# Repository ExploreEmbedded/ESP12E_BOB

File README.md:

# ESP12E_BOB

The ESP8266 ESP12E Wifi Module is now more user friendly with the Explore ESP8266 Wi-Fi Module. It aptly fits on a breadboard 
with all pins taken out. The module goes into programming mode with a single reset switch. 
<a href = "https://www.exploreembedded.com/product/Explore%20ESP8266%20Wi-Fi%20Module">Click here</a> for more details.

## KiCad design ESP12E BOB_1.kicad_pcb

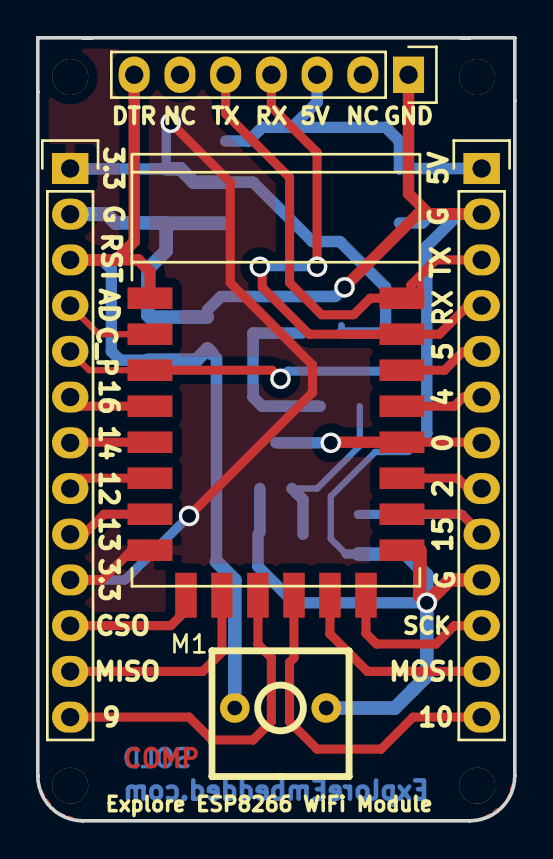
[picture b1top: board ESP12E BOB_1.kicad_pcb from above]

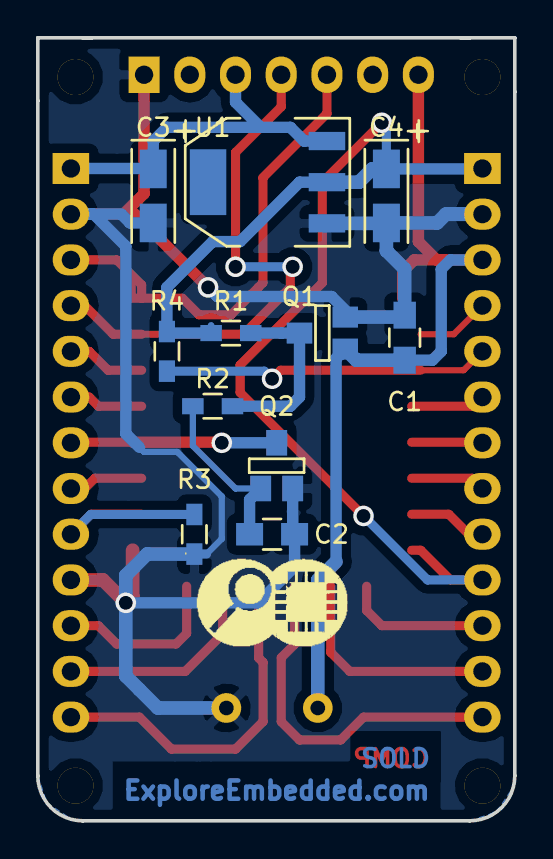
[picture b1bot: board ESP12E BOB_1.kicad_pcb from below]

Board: 2 copper layers, 26.5 x 43.5 mm, 21 parts (12 on the bottom side), 25 nets.

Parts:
C1: 0.1u; C_0805_HandSoldering
C2: 2u2; C_0805_HandSoldering
C3: 4u7; TantalC_SizeA_EIA-3216_Wave
C4: 10u; TantalC_SizeA_EIA-3216_Wave
LOGO: LOGO (2)
M1: ESP-12E
P1: CONN_01X07; Pin_Header_Straight_1x07
P2, P3: CONN_01X13; Pin_Header_Straight_1x13
P4, P5, P6, P7: CONN_01X01; 1pin
Q1, Q2: BSS138; SOT-23-GDS
R1: 470K; R_0603_HandSoldering
R2: 100K; R_0603_HandSoldering
R3: 10K; R_0603_HandSoldering
R4: 47K; R_0603_HandSoldering
SW1: SW_PUSH; SW_PUSH_SMALL_2pin_xl
U1: 1117-3.3; SOT-223

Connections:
+3V3: C4.1, M1.8, P3.1, P3.10, R1.1, R4.1, U1.2
+5V: C3.1, P1.3, P2.1, U1.3
/GPIO0: M1.18, P2.7, Q2.D
/GPIO10: M1.12, P2.13
/MOSI: M1.13, P2.12
/RESET: C1.1, M1.1, P1.7, P3.3, Q1.G, SW1.2
/RX: M1.21, P1.4, P2.4
/SCK: M1.14, P2.11
/TX: M1.22, P1.5, P2.3
GND: C1.2, C2.2, C3.2, C4.2, M1.15, P1.1, P2.2, P2.10, P3.2, Q1.S, Q2.S, R3.1, SW1.1, U1.1
unnamed: C2.1, Q2.G, R2.1
unnamed: M1.2, P3.4
unnamed: M1.3, P3.5, R4.2
unnamed: M1.4, P3.6
unnamed: M1.5, P3.7
unnamed: M1.6, P3.8
unnamed: M1.7, P3.9
unnamed: M1.9, P3.11
unnamed: M1.10, P3.12
unnamed: M1.11, P3.13
unnamed: M1.16, P2.9, R3.2
unnamed: M1.17, P2.8
unnamed: M1.19, P2.6
unnamed: M1.20, P2.5
unnamed: Q1.D, R1.2, R2.2

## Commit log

2015-06-17 test review
2015-07-13 ADDED FILES
2015-07-13 ADDED NEW FILES
2015-07-25 Ident modified
2015-10-28 Changed legend and Connector
2015-11-24 added corrected files
